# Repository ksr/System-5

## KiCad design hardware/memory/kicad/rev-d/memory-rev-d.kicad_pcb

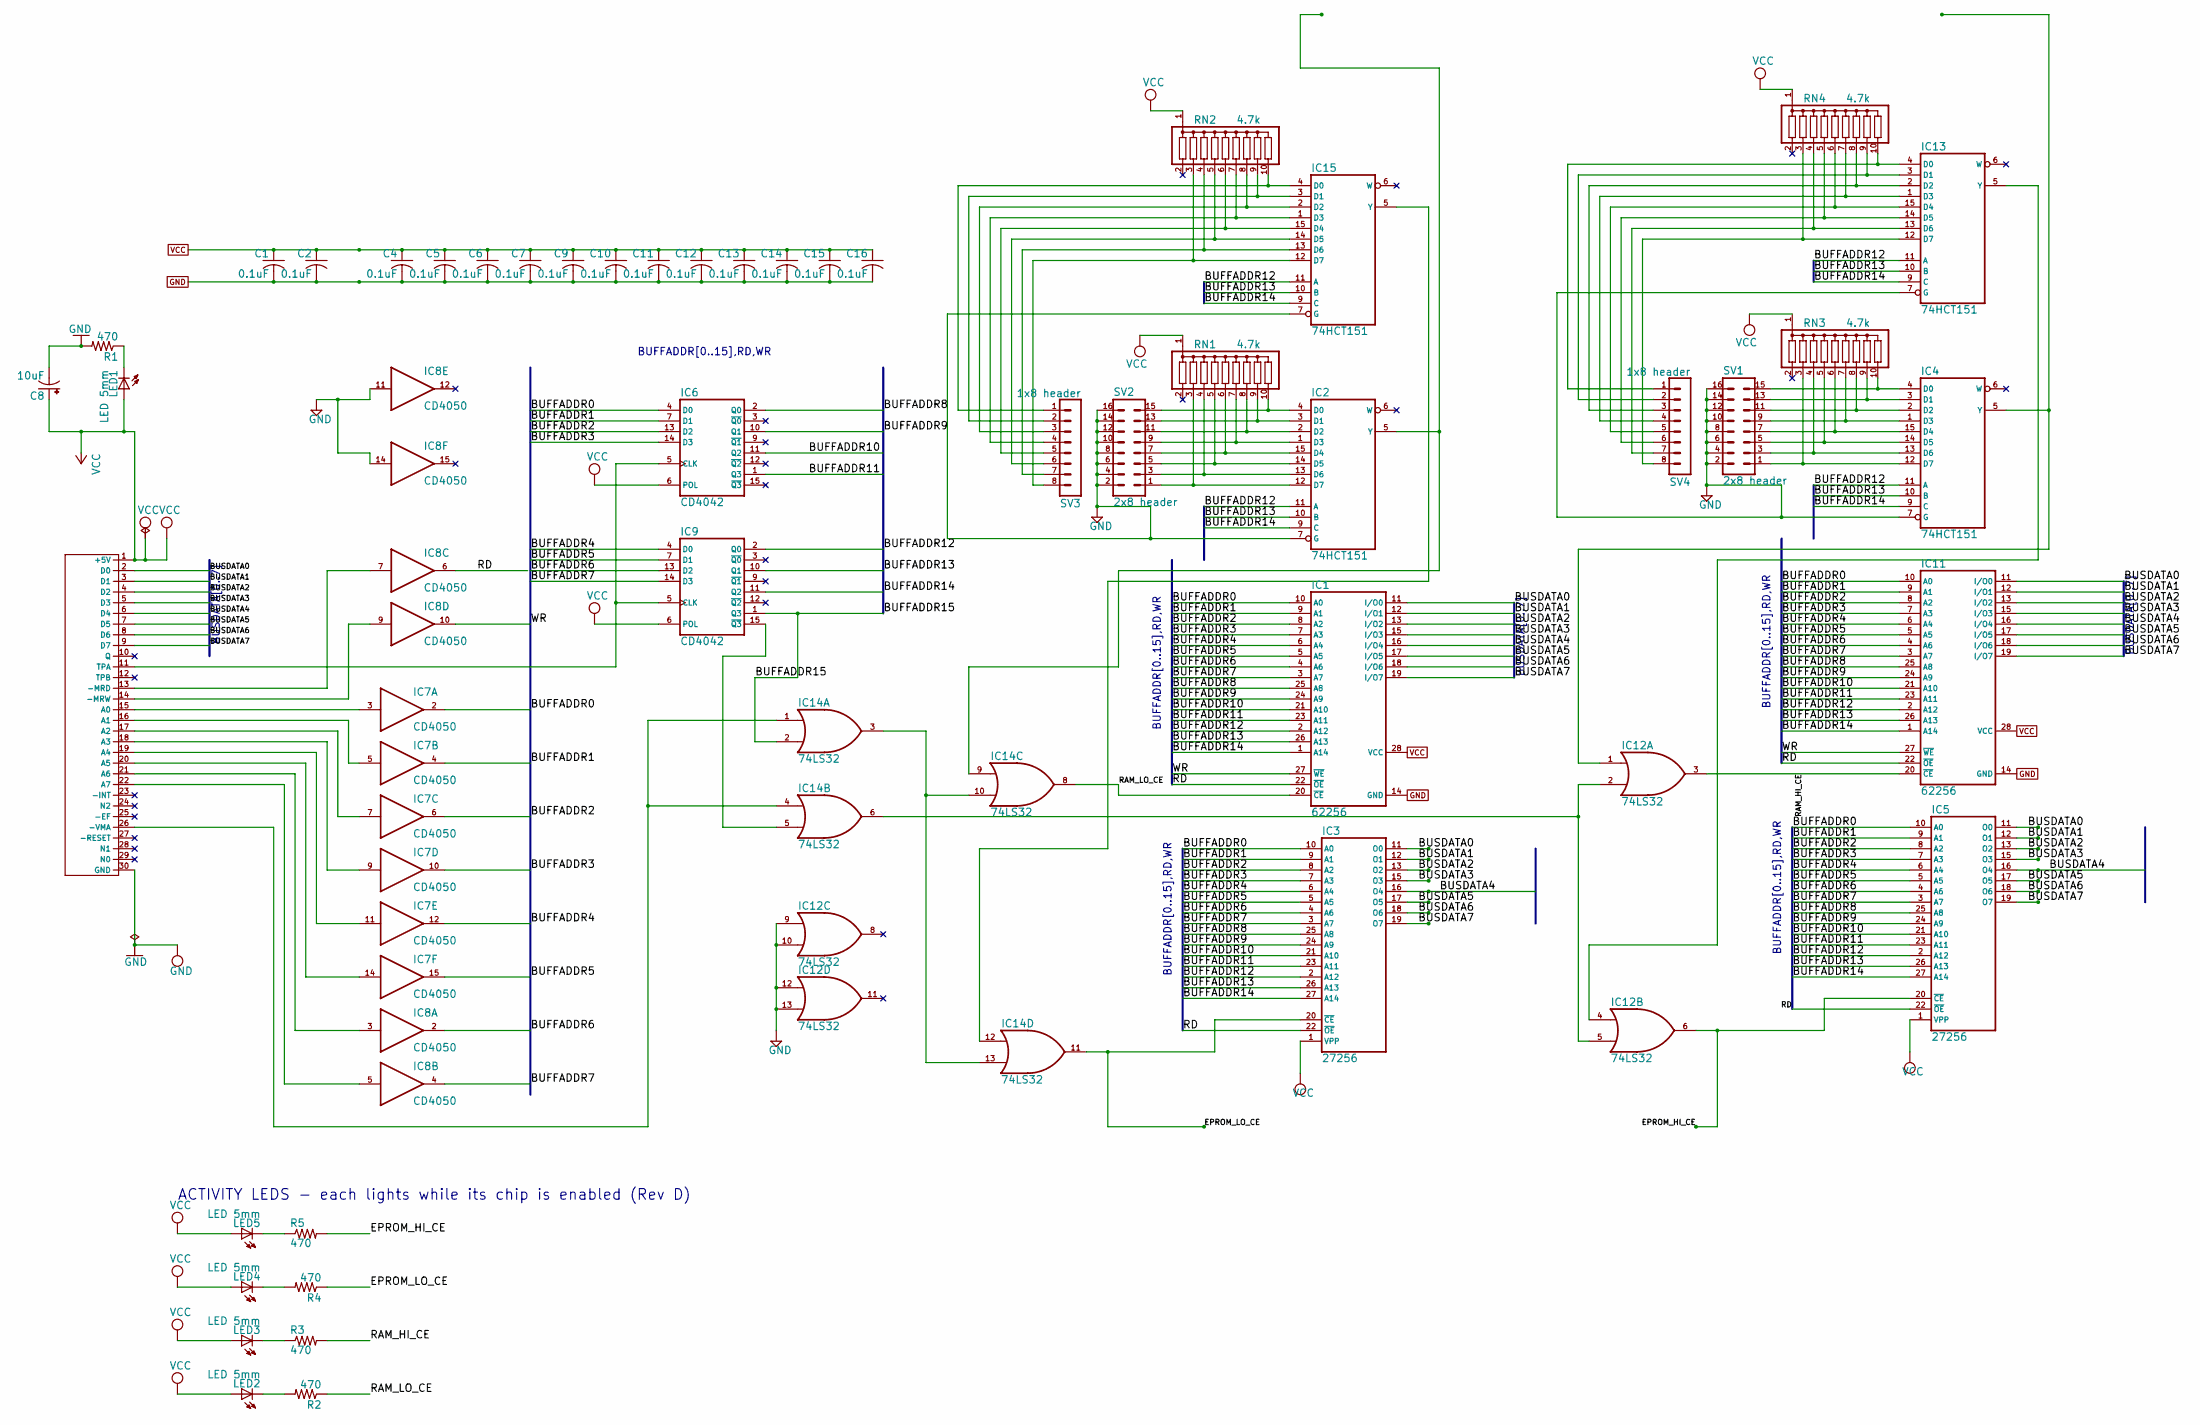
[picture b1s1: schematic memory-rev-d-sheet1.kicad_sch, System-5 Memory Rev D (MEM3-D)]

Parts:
C1, C2, C4, C5, C6, C7, C9, C10, C11, C12, C13, C14, C15, C16: 0.1uF; C025-050X050
C8: 10uF; E2,5-7
IC1, IC11: 62256; DIL28-6
IC2, IC4, IC13, IC15: 74HCT151; DIL16
IC3, IC5: 27256; DIL28
IC6, IC9: CD4042; DIL16
IC7, IC8: CD4050; DIL16
IC12, IC14: 74LS32; DIL14
LED1, LED2, LED3, LED4, LED5: LED 5mm; LED5MM
R1, R2, R3, R4, R5: 470; 0207_7
RN1, RN2, RN3, RN4: 4.7k; SIL10
SV1, SV2: 2x8 header; MA08-2
SV3, SV4: 1x8 header; MA08-1
U$1: System-5 bus 30-pin; C30

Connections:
/Sheet 1/BUFFADDR0: IC1.10 (A0), IC3.10 (A0), IC5.10 (A0), IC6.4 (D0), IC7.2 (O), IC11.10 (A0)
/Sheet 1/BUFFADDR1: IC1.9 (A1), IC3.9 (A1), IC5.9 (A1), IC6.7 (D1), IC7.4 (O), IC11.9 (A1)
/Sheet 1/BUFFADDR2: IC1.8 (A2), IC3.8 (A2), IC5.8 (A2), IC6.13 (D2), IC7.6 (O), IC11.8 (A2)
/Sheet 1/BUFFADDR3: IC1.7 (A3), IC3.7 (A3), IC5.7 (A3), IC6.14 (D3), IC7.10 (O), IC11.7 (A3)
/Sheet 1/BUFFADDR4: IC1.6 (A4), IC3.6 (A4), IC5.6 (A4), IC7.12 (O), IC9.4 (D0), IC11.6 (A4)
/Sheet 1/BUFFADDR5: IC1.5 (A5), IC3.5 (A5), IC5.5 (A5), IC7.15 (O), IC9.7 (D1), IC11.5 (A5)
/Sheet 1/BUFFADDR6: IC1.4 (A6), IC3.4 (A6), IC5.4 (A6), IC8.2 (O), IC9.13 (D2), IC11.4 (A6)
/Sheet 1/BUFFADDR7: IC1.3 (A7), IC3.3 (A7), IC5.3 (A7), IC8.4 (O), IC9.14 (D3), IC11.3 (A7)
/Sheet 1/BUFFADDR8: IC1.25 (A8), IC3.25 (A8), IC5.25 (A8), IC6.2 (Q0), IC11.25 (A8)
/Sheet 1/BUFFADDR9: IC1.24 (A9), IC3.24 (A9), IC5.24 (A9), IC6.10 (Q1), IC11.24 (A9)
/Sheet 1/BUFFADDR10: IC1.21 (A10), IC3.21 (A10), IC5.21 (A10), IC6.11 (Q2), IC11.21 (A10)
/Sheet 1/BUFFADDR11: IC1.23 (A11), IC3.23 (A11), IC5.23 (A11), IC6.1 (Q3), IC11.23 (A11)
/Sheet 1/BUFFADDR12: IC1.2 (A12), IC2.11 (A), IC3.2 (A12), IC4.11 (A), IC5.2 (A12), IC9.2 (Q0), IC11.2 (A12), IC13.11 (A), IC15.11 (A)
/Sheet 1/BUFFADDR13: IC1.26 (A13), IC2.10 (B), IC3.26 (A13), IC4.10 (B), IC5.26 (A13), IC9.10 (Q1), IC11.26 (A13), IC13.10 (B), IC15.10 (B)
/Sheet 1/BUFFADDR14: IC1.1 (A14), IC2.9 (C), IC3.27 (A14), IC4.9 (C), IC5.27 (A14), IC9.11 (Q2), IC11.1 (A14), IC13.9 (C), IC15.9 (C)
/Sheet 1/BUFFADDR15: IC9.1 (Q3), IC14.2 (I1)
/Sheet 1/BUSDATA0: IC1.11 (I/O0), IC3.11 (O0), IC5.11 (O0), IC11.11 (I/O0), U$1.2 (D0)
/Sheet 1/BUSDATA1: IC1.12 (I/O1), IC3.12 (O1), IC5.12 (O1), IC11.12 (I/O1), U$1.3 (D1)
/Sheet 1/BUSDATA2: IC1.13 (I/O2), IC3.13 (O2), IC5.13 (O2), IC11.13 (I/O2), U$1.4 (D2)
/Sheet 1/BUSDATA3: IC1.15 (I/O3), IC3.15 (O3), IC5.15 (O3), IC11.15 (I/O3), U$1.5 (D3)
/Sheet 1/BUSDATA4: IC1.16 (I/O4), IC3.16 (O4), IC5.16 (O4), IC11.16 (I/O4), U$1.6 (D4)
/Sheet 1/BUSDATA5: IC1.17 (I/O5), IC3.17 (O5), IC5.17 (O5), IC11.17 (I/O5), U$1.7 (D5)
/Sheet 1/BUSDATA6: IC1.18 (I/O6), IC3.18 (O6), IC5.18 (O6), IC11.18 (I/O6), U$1.8 (D6)
/Sheet 1/BUSDATA7: IC1.19 (I/O7), IC3.19 (O7), IC5.19 (O7), IC11.19 (I/O7), U$1.9 (D7)
/Sheet 1/EPROM_HI_CE: IC5.20 (~CE), IC12.6 (O), R5.2
/Sheet 1/EPROM_LO_CE: IC3.20 (~CE), IC14.11 (O), R4.1
/Sheet 1/RAM_HI_CE: IC11.20 (~CE), IC12.3 (O), R3.2
/Sheet 1/RAM_LO_CE: IC1.20 (~CE), IC14.8 (O), R2.1
/Sheet 1/RD: IC1.22 (~OE), IC3.22 (~OE), IC5.22 (~OE), IC8.6 (O), IC11.22 (~OE)
/Sheet 1/WR: IC1.27 (~WE), IC8.10 (O), IC11.27 (~WE)
GND: C1.2, C2.2, C4.2, C5.2, C6.2, C7.2, C8.-, C9.2, C10.2, C11.2, C12.2, C13.2, C14.2, C15.2, C16.2, IC1.14 (GND), IC2.7 (G), IC2.8 (GND), IC3.14 (GND), IC4.7 (G), IC4.8 (GND), IC5.14 (GND), IC6.8 (GND), IC7.8 (GND), IC8.8 (GND), IC8.11 (I), IC8.14 (I), IC9.8 (GND), IC11.14 (GND), IC12.7 (GND), IC12.9 (I0), IC12.10 (I1), IC12.12 (I0), IC12.13 (I1), IC13.7 (G), IC13.8 (GND), IC14.7 (GND), IC15.7 (G), IC15.8 (GND), R1.2, SV1.2, SV1.4, SV1.6, SV1.8, SV1.10, SV1.12, SV1.14, SV1.16, SV2.2, SV2.4, SV2.6, SV2.8, SV2.10, SV2.12, SV2.14, SV2.16, U$1.30 (GND)
unnamed: IC2.4 (D0), RN1.10, SV2.15
unnamed: IC2.3 (D1), RN1.9, SV2.13
unnamed: IC2.2 (D2), RN1.8, SV2.11
unnamed: IC2.1 (D3), RN1.7, SV2.9
unnamed: IC2.15 (D4), RN1.6, SV2.7
unnamed: IC2.14 (D5), RN1.5, SV2.5
unnamed: IC2.13 (D6), RN1.4, SV2.3
unnamed: IC2.12 (D7), RN1.3, SV2.1
unnamed: IC4.4 (D0), RN3.10, SV1.15
unnamed: IC4.3 (D1), RN3.9, SV1.13
unnamed: IC4.2 (D2), RN3.8, SV1.11
unnamed: IC4.1 (D3), RN3.7, SV1.9
unnamed: IC4.15 (D4), RN3.6, SV1.7
unnamed: IC4.14 (D5), RN3.5, SV1.5
unnamed: IC4.13 (D6), RN3.4, SV1.3
unnamed: IC4.12 (D7), RN3.3, SV1.1
unnamed: IC6.5 (CLK), IC9.5 (CLK), U$1.11 (TPA)
unnamed: IC7.3 (I), U$1.15 (A0)
unnamed: IC7.5 (I), U$1.16 (A1)
unnamed: IC7.7 (I), U$1.17 (A2)
unnamed: IC7.9 (I), U$1.18 (A3)
unnamed: IC7.11 (I), U$1.19 (A4)
unnamed: IC7.14 (I), U$1.20 (A5)
unnamed: IC8.3 (I), U$1.21 (A6)
unnamed: IC8.5 (I), U$1.22 (A7)
unnamed: IC8.7 (I), U$1.13 (-MRD)
unnamed: IC8.9 (I), U$1.14 (-MRW)
unnamed: IC4.5 (Y), IC12.1 (I0)
unnamed: IC12.2 (I1), IC12.5 (I1), IC14.6 (O)
unnamed: IC12.4 (I0), IC13.5 (Y)
unnamed: IC13.4 (D0), RN4.10, SV4.1
unnamed: IC13.3 (D1), RN4.9, SV4.2
unnamed: IC13.2 (D2), RN4.8, SV4.3
unnamed: IC13.1 (D3), RN4.7, SV4.4
unnamed: IC13.15 (D4), RN4.6, SV4.5
unnamed: IC13.14 (D5), RN4.5, SV4.6
unnamed: IC13.13 (D6), RN4.4, SV4.7
unnamed: IC13.12 (D7), RN4.3, SV4.8
unnamed: IC14.1 (I0), IC14.4 (I0), U$1.26 (-VMA)
unnamed: IC14.3 (O), IC14.10 (I1), IC14.13 (I1)
unnamed: IC9.15 (~Q3), IC14.5 (I1)
unnamed: IC2.5 (Y), IC14.9 (I0)
unnamed: IC14.12 (I0), IC15.5 (Y)
unnamed: IC15.4 (D0), RN2.10, SV3.1
unnamed: IC15.3 (D1), RN2.9, SV3.2
unnamed: IC15.2 (D2), RN2.8, SV3.3
unnamed: IC15.1 (D3), RN2.7, SV3.4
unnamed: IC15.15 (D4), RN2.6, SV3.5
unnamed: IC15.14 (D5), RN2.5, SV3.6
unnamed: IC15.13 (D6), RN2.4, SV3.7
unnamed: IC15.12 (D7), RN2.3, SV3.8
unnamed: LED1.K (C), R1.1
unnamed: LED2.K (C), R2.2
unnamed: LED3.K (C), R3.1
unnamed: LED4.K (C), R4.2
unnamed: LED5.K (C), R5.1
VCC: C1.1, C2.1, C4.1, C5.1, C6.1, C7.1, C8.+, C9.1, C10.1, C11.1, C12.1, C13.1, C14.1, C15.1, C16.1, IC1.28 (VCC), IC2.16 (VCC), IC3.1 (VPP), IC3.28 (VCC), IC4.16 (VCC), IC5.1 (VPP), IC5.28 (VCC), IC6.6 (POL), IC6.16 (VCC), IC7.1 (VCC), IC8.1 (VCC), IC9.6 (POL), IC9.16 (VCC), IC11.28 (VCC), IC12.14 (VCC), IC13.16 (VCC), IC14.14 (VCC), IC15.16 (VCC), LED1.A, LED2.A, LED3.A, LED4.A, LED5.A, RN1.1, RN2.1, RN3.1, RN4.1, U$1.1 (+5V)

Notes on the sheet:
BUFFADDR[0..15],RD,WR
BUSDATA[0..7]
ACTIVITY LEDS - each lights while its chip is enabled (Rev D)

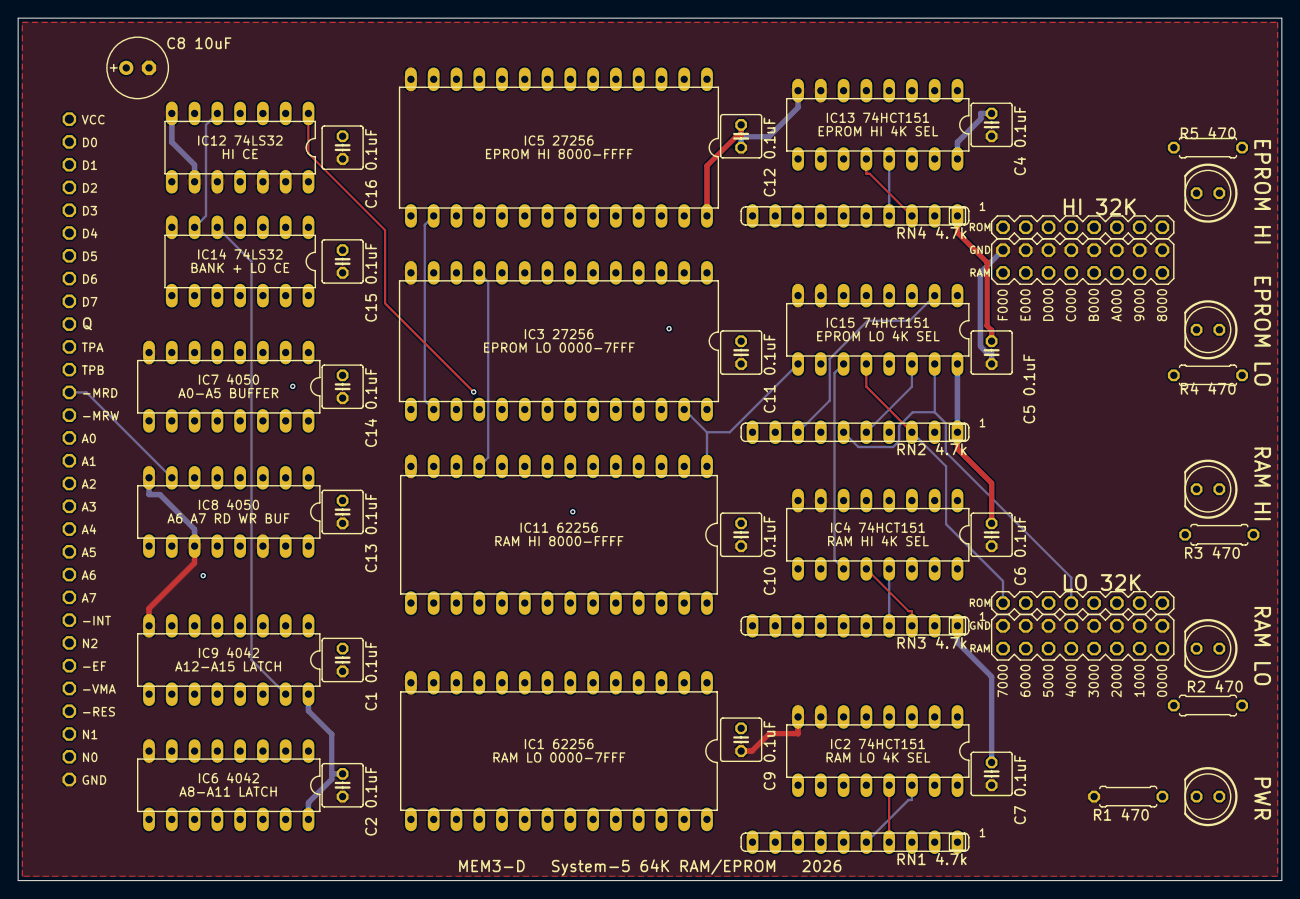
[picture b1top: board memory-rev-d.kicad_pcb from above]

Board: 4 copper layers, 140.9 x 96.2 mm, 48 parts (0 on the bottom side), 88 nets.

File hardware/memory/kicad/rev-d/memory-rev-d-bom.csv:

"Reference","Value","Footprint","QUANTITY"
"C1,C2,C4-C7,C9-C16","0.1uF","memory-rev-d-eagle:C025-050X050","14"
"C8","10uF","memory-rev-d-eagle:E2,5-7","1"
"IC1,IC11","62256","memory-rev-d-eagle:DIL28-6","2"
"IC2,IC4,IC13,IC15","74HCT151","memory-rev-d-eagle:DIL16","4"
"IC3,IC5","27256","memory-rev-d-eagle:DIL28","2"
"IC6,IC9","CD4042","memory-rev-d-eagle:DIL16","2"
"IC7,IC8","CD4050","memory-rev-d-eagle:DIL16","2"
"IC12,IC14","74LS32","memory-rev-d-eagle:DIL14","2"
"LED1-LED5","LED 5mm","memory-rev-d-eagle:LED5MM","5"
"R1-R5","470","memory-rev-d-eagle:0207_7","5"
"RN1-RN4","4.7k","memory-rev-d-eagle:SIL10","4"
"SV1,SV2","2x8 header","memory-rev-d-eagle:MA08-2","2"
"SV3,SV4","1x8 header","memory-rev-d-eagle:MA08-1","2"
"U$1","System-5 bus 30-pin","memory-rev-d-eagle:C30","1"
